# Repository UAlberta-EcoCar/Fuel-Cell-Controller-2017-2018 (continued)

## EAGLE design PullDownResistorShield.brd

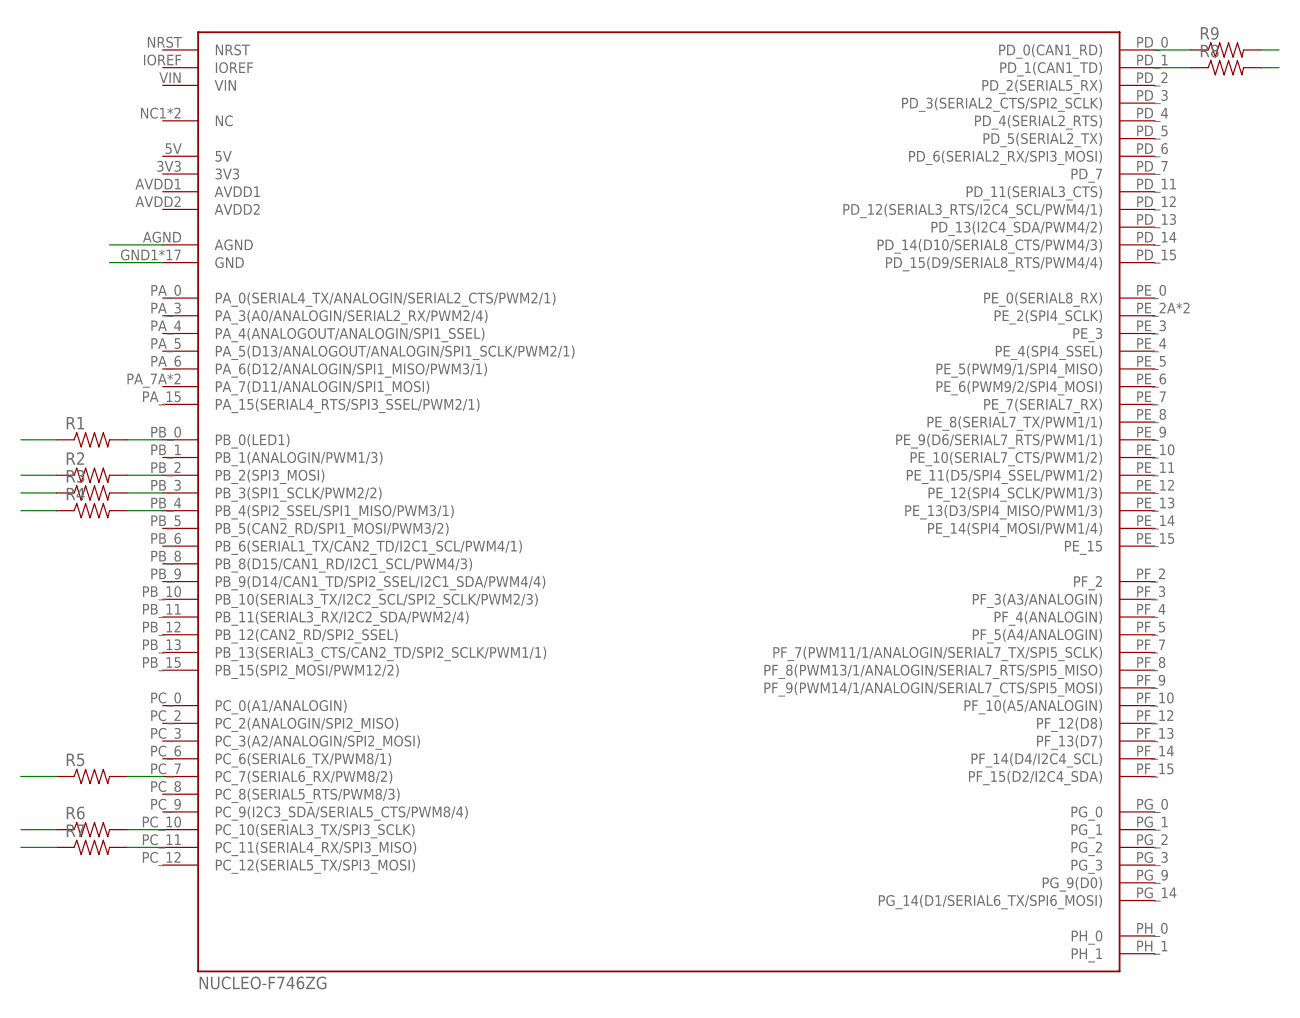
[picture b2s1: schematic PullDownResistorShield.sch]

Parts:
R1, R2, R3, R4, R5, R6, R7, R8, R9: RESISTORPTH-1/4W; AXIAL-0.4
U$1: NUCLEO-F746ZGNUCLEO-F746ZG; NUCLEO-F746ZG

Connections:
GND: R1.P$1 (1), R2.P$1 (1), R3.P$1 (1), R4.P$1 (1), R5.P$1 (1), R6.P$1 (1), R7.P$1 (1), R8.P$2 (2), R9.P$2 (2), U$1.AGND, U$1.GND1 (GND), U$1.GND2 (GND), U$1.GND3 (GND), U$1.GND4 (GND), U$1.GND5 (GND), U$1.GND6 (GND), U$1.GND7 (GND), U$1.GND8 (GND), U$1.GND9 (GND), U$1.GND10 (GND), U$1.GND11 (GND), U$1.GND12 (GND), U$1.GND13 (GND), U$1.GND14 (GND), U$1.GND15 (GND), U$1.GND16 (GND), U$1.GND17 (GND)
unnamed: R1.P$2 (2), U$1.PB_0 (PB_0(LED1))
unnamed: R2.P$2 (2), U$1.PB_2 (PB_2(SPI3_MOSI))
unnamed: R3.P$2 (2), U$1.PB_3 (PB_3(SPI1_SCLK/PWM2/2))
unnamed: R4.P$2 (2), U$1.PB_4 (PB_4(SPI2_SSEL/SPI1_MISO/PWM3/1))
unnamed: R5.P$2 (2), U$1.PC_7 (PC_7(SERIAL6_RX/PWM8/2))
unnamed: R6.P$2 (2), U$1.PC_10 (PC_10(SERIAL3_TX/SPI3_SCLK))
unnamed: R7.P$2 (2), U$1.PC_11 (PC_11(SERIAL4_RX/SPI3_MISO))
unnamed: R9.P$1 (1), U$1.PD_0 (PD_0(CAN1_RD))
unnamed: R8.P$1 (1), U$1.PD_1 (PD_1(CAN1_TD))

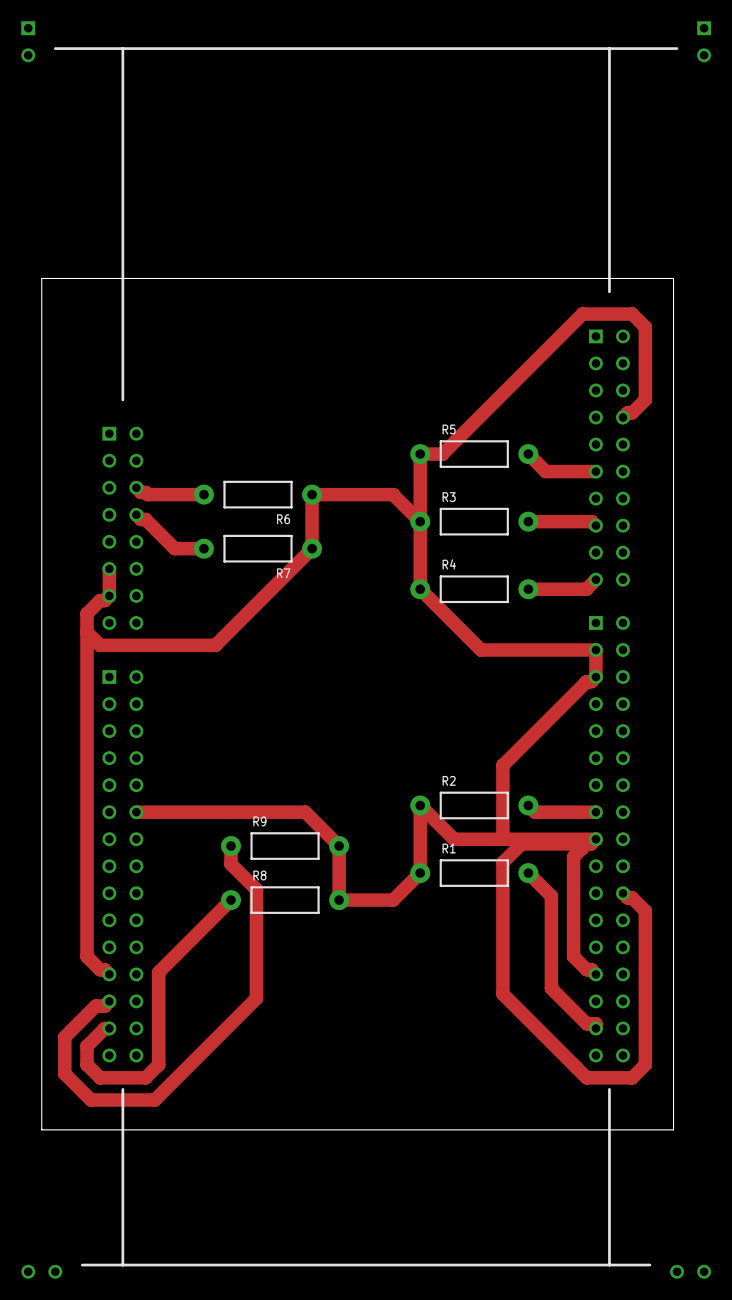
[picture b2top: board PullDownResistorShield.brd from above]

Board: 2 copper layers, 59.4 x 80.0 mm, 10 parts (0 on the bottom side), 10 nets.

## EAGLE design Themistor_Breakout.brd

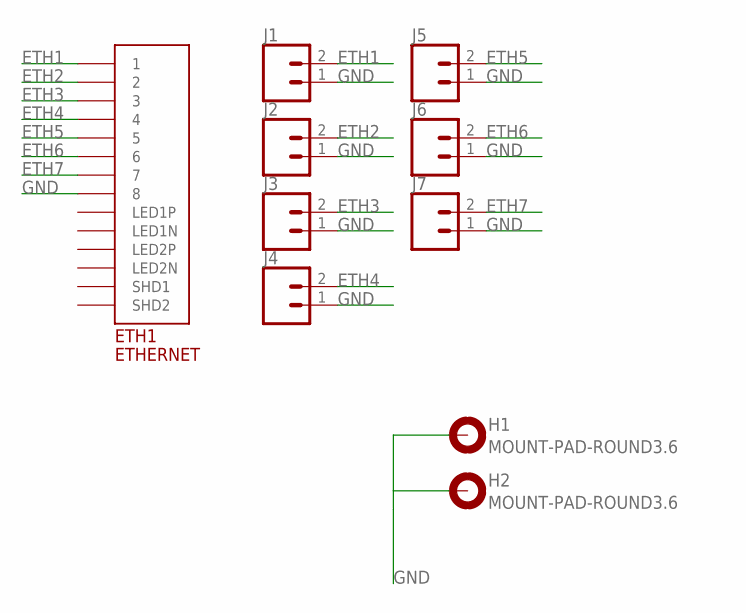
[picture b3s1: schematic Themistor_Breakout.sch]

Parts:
ETH1: ETHERNET; A122645-ND
H1, H2: MOUNT-PAD-ROUND3.6; 3,6-PAD
J1, J2, J3, J4, J5, J6, J7: CONN_023.5MM; SCREWTERMINAL-3.5MM-2

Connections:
ETH1: ETH1.P$1 (1), J1.2
ETH2: ETH1.P$2 (2), J2.2
ETH3: ETH1.P$3 (3), J3.2
ETH4: ETH1.P$4 (4), J4.2
ETH5: ETH1.P$5 (5), J5.2
ETH6: ETH1.P$6 (6), J6.2
ETH7: ETH1.P$7 (7), J7.2
GND: ETH1.P$8 (8), H1.B3,6, H2.B3,6, J1.1, J2.1, J3.1, J4.1, J5.1, J6.1, J7.1

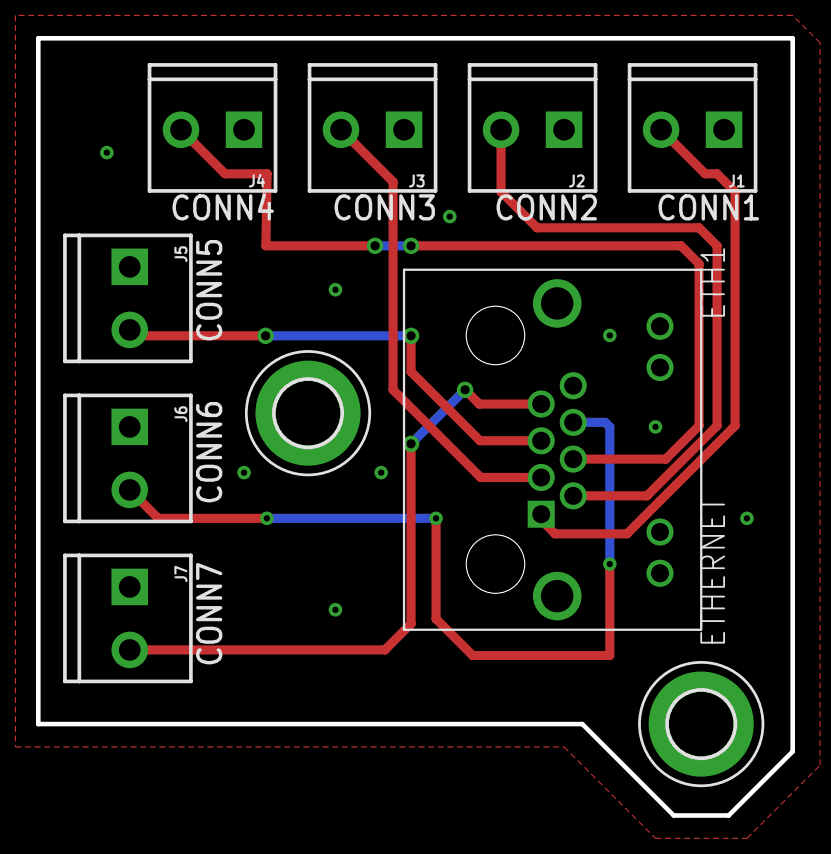
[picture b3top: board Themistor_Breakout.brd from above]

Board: 2 copper layers, 41.9 x 43.2 mm, 10 parts (0 on the bottom side), 8 nets.

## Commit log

2017-10-04 Created Fuel Cell Controller Schematic
2017-10-04 Added FCC_library that has three parts needed for board
2017-10-04 Added up to date library
2017-10-07 Added a Name to STM's Symbol
2017-10-07 Changed STM's Symbol Name
2017-10-07 Added some labels to Ethernet Connectors
2017-10-07 Created RJ45 thermistor breakout board
2017-10-07 Changed gitignore file
2017-10-12 Added a couple of connections and a part to library
2017-10-12 Almost finished connection to OPENLOG. Not sure how reset pin works.
2017-10-13 Finished Ethernet Conn Schematic
2017-10-13 added a few more connections and set up reset pin
2017-10-14 Finished Openlog. Reset will be controlled by microcontroller
2017-10-14 Added Bluetooth
2017-10-14 Removed stray gnd traces from autorouter
2017-10-14 Added mounting holes to thermistor breakout
2017-10-14 Finished most serial connections
2017-10-14 Added humidity sensor to parts library
2017-10-14 I dunno i changed something with the libraries
2017-10-21 Started Fans Schematic
2017-10-25 Added UMFT234XF FTDI part
2017-10-25 Implemented FTDI Chip on the schematic
2017-10-28 added some connections
2017-10-28 added a few connections
2017-10-28 added some buffers
2017-10-28 buffer changes
2017-10-28 Added humidity sensor
2017-10-28 Didn't really do anything
2017-10-28 Created new sheets for Valves, Fans, FC LP Filter
2017-10-30 Added photocouplers
2017-10-30 Added rs232 to mass flow meter
2017-10-31 Added DS3231 RTC
2017-10-31 Made it look prettier
2017-11-04 Added the ADC into the library
2017-11-04 Added ADC to schematic
2017-11-05 Added value for capacitor between 3v3 and gnd on rtc
2017-11-06 Working on routing now. Deleted caps and resistors on RTC
2017-11-06 lol kk
2017-11-07 Added a couple of indicator LEDs
2017-11-07 Added TLV2404 Op-amp part (with Dil14 package)
2017-11-07 Changed resistors and caps to 0805; need to spec out some decoupling capacitors, add LED's, and complete low-pass filter with op-amp
2017-11-07 Added a few notes to schematic
2017-11-08 Added a couple indicator LED's and speced out parts on digikey. Added connections to NUCLEO. Will create a part for the RGB LED next and implement it
2017-11-08 Added the 5060BRG4 RGB LED to the library
2017-11-08 Implemented all indicator LED's, including the RGB one
2017-11-09 Added another screw terminal and voltage division for mass flow meter and connected it to the external ADC
2017-11-09 Added extra backup rs232 port
2017-11-09 Changed the values and number of decoupling capacitors
2017-11-09 Added push button
2017-11-09 Added electrolytic decoupling capacitors and start signal
2017-11-09 Implemented op amp for low-pass filter
2017-11-11 made unneccessary backup
2017-11-11 Added starter relay and did more board layout
2017-11-13 Added display, fixed power supplies
2017-11-13 Started routing
2017-11-13 Continued routing
2017-11-14 Labelled RJ45 Connectors
2017-11-14 Added PWR indicator LEDS
2017-11-14 Deleted Start Screw Terminal
2017-11-15 Added some changes in the Schematic to the Board
2017-11-17 Continued Routing the FCC Board
2017-11-20 Routing complete! Need to check the two airwires between nucleo pins
2017-11-24 Some Updates
2017-11-25 Started Cleaning up the Silk Screen
2017-11-26 Deleted extra rs232 and added a capacitor to the ESTOP signal
2017-11-27 Moved capacitor on estop
2017-11-28 Switched P Mosfet with a n mosfet
2017-11-30 Adjusted how nucleo was powered and adding voltage dividers to pressure sensors
2017-11-30 Added pressure sensor voltage dividers to schematic
2017-11-30 Added Pull Up resistors to thermistor inputs
2017-11-30 ReRouted a few traces for resistors
2017-11-30 Moved Schematic Around a Bit
2017-12-02 Changed DSUB connector pinouts
2017-12-05 Gerbers Generated
2017-12-05 Remade thermistor breakout gerbers
2017-12-09 Added a few resistor values
2017-12-31 fixed pin spacing on Nucleo part
2017-12-31 updated brd file with new nucleo part
2017-12-31 fixed board routing
2018-01-02 Generated Gerbers
2018-03-18 Pull down resistor shield
2018-05-29 Made some changes to the FCC board: -Added pull down resistors -Added master power switch -Added power selector switch -Fixed PMOS circuits -Updated PMOS symbol -Decreased signal trace size
2018-07-10 Changed wiring to mass flow meter, part pin numbering is wrong and needs to be changed, mass flow meter needs a serial cable without NULL-Terminal
2018-07-12 Removed power switch, moved poer supply selector from slide switch to header short, moved cap_curr off nucleo and onto the external adc
2018-07-14 updated rj 11 part
